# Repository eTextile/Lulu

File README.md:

# Lulu-MCU

**Programming light into textile**

Lulu is a hardware solution that interfaces between an LED light source, an optic fiber strand or bundle and soft circuit connections.
Providing an optic fiber connection toolset and workflow for E-Textiles and Wearable Technology applications.

### About The project
Lulu is providing a simple, reliable toolset for people who want to use side glow optical fibers in their eTextile and wearable projects.
Use of light in textile and fashion design is becoming more and more common and many schools started to teach this subject as a part of their textile design curriculum.
Optic fibers could be embedded in textiles as embroidery, in weaving, knitting and knotting process and many textile designs have been realized in recent years.
But often the designers lack the toolset for connecting the light sources with the embedded optic fibers, resulting in re-purposing bulky connectors and technology and hiding them behind the textiles.
Currently, each designer has to come up with their own re-purposed or DIY solution.
Lulu is a connector that optimizes the efficiency of the connection between the light source and the optical fibers to get a strong illumination.
Instead of struggling to solve the light source and connection problem, the designer can concentrate on the aesthetic and textile making process issues.

### Lulu branches
- **Lulu-star (master)**
  - This branch provide a tiny PCB with a 200mA LED, PWM driver and an optic fiber connector.
- **Lulu-daisy**
  - This branch provide a tiny PCB with an addressable LED (WS2812-mini, Dotstar, etc) and an optic fiber connector.
- **Lulu-MCU**
  - This branch provide a tiny PCB with a built in MCU (ATTiny10) that allow one-wire communication bus system.
- **Lulu**
  - This branch provide a motherboard (Lucette) that drive up to 16 Lulu that only contain a power LED and an optic fiber connector.

### Development tools & DOCs
 * **Web page**: [http://lulu.eTextile.org](http://lulu.eTextile.org "The project Web page")
 * **Kobakant web page**: [http://www.kobakant.at/KOBA/lulu-developments](http://www.kobakant.at/KOBA/lulu-developments "Kobakant project Web page")
 * **Repository**: [https://github.com/eTextile/Lulu/tree/master](https://github.com/eTextile/Lulu/tree/master "The project repository")
 * **License**: [CC-BY-SA](https://github.com/eTextile/Lulu/blob/master/LICENSE "See the Lulu license project")
 * **Video**: [Lulu project by Hannah](https://www.youtube.com/watch?v=drAoLd_eUWk "Lulu project Introduction")
 * **Video**: [Lulu project by Maurin](https://vimeo.com/249171264 "eTextile bus solution")
 * **Mail**: [lulu@etextile.org](mailto:lulu@etextile.org "eMail us")
 * **IRC**: [Riot](https://vector.im/develop/#/room/#lulu:matrix.org "Join us on the chat to collaborate in the development")
 * **Pictures**: [Flickr](https://www.flickr.com/groups/3908991@N25/ "Share your Lulu pictures project")

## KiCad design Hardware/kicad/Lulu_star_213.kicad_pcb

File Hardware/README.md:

# Lulu-MCU / Hardware
**Programming light into textile**

# Lulu-MCU

## Hardware design
This branch of the Lulu project is using a 200mA power LED with current current circuitry.
As the project is focussing on embedded electronics we chosed an high power LED ; OSRAM OSLON SX seeking 200 mA/h 
Then it can be 5 hour of autonomy with a 1000 mA Lypo battery.
The LED is also providing a narrow angle (60°) this helps to focus the light in to the optic fiber wafer.
    See datasheet: https://github.com/eTextile/Lulu/blob/master/Hardware/DOCs/LY_CN5M.pdf
The brass tube connector have been selected to fit the outer diameter of the LED optics.
The PCB triangle shape have been selected to fit the zero waste production process.
All the components are SMD package to reduce the size and price of th PCB.
We have been experiencing a new way to hand solder the LED on the edge of the PCB but it is still not so handy.
Custom tooling will be designed and tested to help in that soldering process.

## Release notes
### Lulu-MCU 4.0.0
- Initial release (forked from Lulu-star 2.1.3)

## Lulu-MCU connecting
- [VCC] (+) 3.3 to 5 Voltes
- [GND] (-) GND
- [DATA] oneWire data bus

        +---+--------------+-------------------+-----
        |   |              |                   |
    + __|__ |              |                   |
    -  ___  |              |                   |
        |   |              |                   |
        +---|--------------|--+----------------|--+--
        |   |              |  |                |  |
        |   |            __|__|__            __|__|__
       _|___|_           \ +  - /            \ +  - /
      | +   - |           \    /              \    /
      |   M   |            \  /                \  /
      |   C   |             \/                  \/
      |   U   |              |                   |
      |       |--------------------- DATA ------------
      |_______|

## Lulu-MCU Powering
The Lulu-MCU board must be powered with a voltage betwin 3.3V to 5V.
DO NOT USE 3V single coin battery - voltage is too low and it will not work for long.
Prefer the use of rechargeable Lipo battery with small Lipo charger.
- https://www.powerstream.com/thin-primary-lithium.htm
- Charger technology
- Low discharge protection

## Lulu-MCU built-in LED driver
### Constant current source circuitry

**References**
- https://learn.adafruit.com/pixie-3-watt-smart-chainable-led-pixels/design
- http://www.instructables.com/id/Power-LED-s---simplest-light-with-constant-current/
- https://scienceprog.com/building-simple-constant-current-power-led-driver/
- http://www.pcbheaven.com/userpages/LED_driving_and_controlling_methods/?topic=worklog&p=3

### Circuit part list
| Designator                                      | MPN                       | Package                | Price per unit | Weblink                |
| ----------------------------------------------- | ------------------------- | -----------------------|--------------- |------------------------|
| Power LED / OSRAM 200mA                         | LY CN5M                   |                        | 0.65 $         | [LY-CN5M](https://fr.aliexpress.com/item/OSRAM-OSLON-SX-High-Power-LED-0-5W-3030-Yellow-LY-CN5M/32865040281.html?spm=a2g0s.9042311.0.0.27426c371XVtDl) |
| Q1 - large N-channel MOSFET                     | IRLML2060TRPBF            | SOT-23                 | 0,126 €        | [IRLML2060TRPBF](https://www.digikey.com/product-detail/en/infineon-technologies/IRLML2060TRPBF/IRLML2060TRPBFCT-ND/2271917) |
| T1 - small NPN transistor                       | MMBT2222A                 | SOT-23                 | 0,0412 €       | [MMBT2222A](https://www.digikey.com/product-detail/en/diodes-incorporated/MMBT2222A-7-F/MMBT2222A-FDICT-ND/815723) |
| R1 - 47k-ohm resistor                           | RT0603DRD0747KL           | 0603                   | 0,0147 €       | [R-47k-ohm ](https://www.digikey.com/product-detail/en/yageo/RT0603DRD0747KL/311-47KDCT-ND/1035828) |
| R2 - current set resistor - 2.7 ohms 1/4 watt   |                           | 1206                   | 0,0246 €       | [R-2.7-ohm](https://fr.farnell.com/walsin/wr12w2r70ftl/resist-couche-epaisse-2-7r-1-0/dp/2668305) |
| R3 - 10k pull-down resistor                     | RT0603DRD0710KL           | 0603                   | 0,     €       | [R-10k-ohm](https://www.digikey.com/product-detail/en/yageo/RT0603DRD0710KL/311-10KDCT-ND/1035680) |
| ATTiny10                                        |                           | SOT-                   | 0,     €       | [ATTiny10](...) |

**R2** is used to set the current limit and this doesn't depends on the voltage supply VDD.
**Q1** is used as a variable resistor. **Q1** starts out turned on by **R1**.
**T1** is used as an over-current sensing switch, and **R2** is the "sense resistor" that triggers **T1** when too much current is flowing.
The main current flow is through the LED's, through **Q1**, and through **R2**.
When too much current flows through **R2**, **T1** will start to turn on, which starts turning off **Q1**. Turning off **Q1** reduces the current through the LED's and **R2**.
So we've created a **feedback loop**, which continuously tracks the current and keeps it exactly at the set point at all times.
The NPN transistors **T1** have a specified 0.6V drop between base and emitter when on.
This means the voltage across their respective shunt resistors **R2** will always be 0.6V.
According to Ohm’s law, this means that the current through them will be '0.6 V / 2.7 Ohm', or about 222mA.

## PCB manufacturing characteristics
  - Base Material : FR-4 TG13
  - No. of Layers : 2 layers
  - PCB Thickness : 1 mm
  - PCB Color : Yelow
  - Surface Finish : HASL
  - Minimum Solder Mask Dam : 0.4 mm
  - Copper Weight : 1oz (35 µm)
    - For 300 mA we nead 0.15mm copper traces (https://www.4pcb.com/trace-width-calculator.html)
  - Minimum Drill Hole Size : 0.3 mm
  - Trace Width / Spacing : 5/5 mil
  - Blind or Buried Vias : NO
  - Plated Half-holes / Castellated Holes : YES
  - Impedance Control : NO

### Extra Part list
| Part                       | REF                      | Price per unit   | Weblink        |
| -------------------------- | ------------------------ | -----------------|--------------- |
| Brass tube                 | 2 mm Hole 5-10 mm Length |                  |                |
| JTE connector              | 1.5 / 8 mm               |                  |                |
| Optical fibres PMMA        | 0.25 mm x 35 pce         |                  |                |
| Optical fibres TPU         | 1.5, 2, 3 mm             |                  |                |
| Optical fibres tube + core |                          |                  | [www.leds-and-more.de](https://www.leds-and-more.de/catalog/15mm-lwl-lichtwellenleiter-lichtleiter-seitlich-leuchtend-p-1937.html?osCsid=2me5dl4q5amcvgb6tnbqfd87i5) |
| eTextile bus               |                          |                  |                |

## TODO
- [ ] Add ATTiny10 ont the KiCad desin
- [ ] Add POGO PINs on the PCB to flash the ATTiny10
- [ ] Change the PCB shape to put the tube angle to 90° from the e-Textile bus
- [ ] cool ref: https://hackaday.io/project/179554-tinyicoc

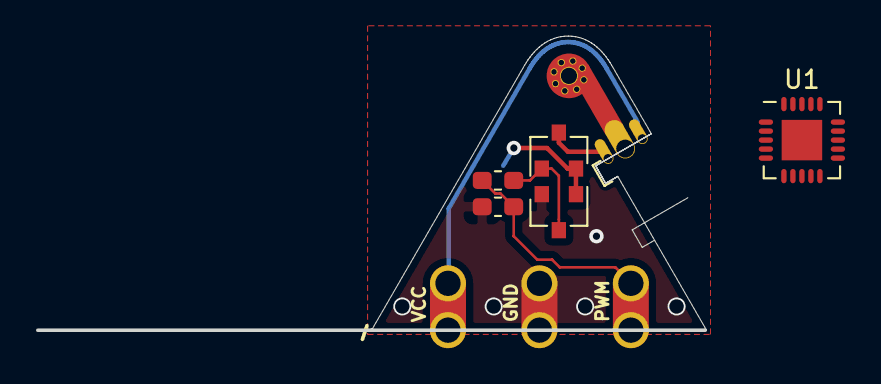
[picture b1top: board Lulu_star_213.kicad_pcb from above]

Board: 2 copper layers, 18.6 x 16.3 mm, 8 parts (1 on the bottom side), 7 nets.

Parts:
J1: Conn_01x03_Female; Lulu_plug_3_spaced
LED1: LED_PAD; Lulu_side_LED
Q1: Q_NMOS_GSD; SOT-23
R1: 47 K; R_0603_1608Metric_Pad1.05x0.95mm_HandSolder
R2: 2.7 Ohm; R_1206_3216Metric_Pad1.42x1.75mm_HandSolder
R3: 10 K; R_0603_1608Metric_Pad1.05x0.95mm_HandSolder
T1: Q_NPN_BEC; SOT-23
U1: ATtiny85-20MU; QFN-20-1EP_4x4mm_P0.5mm_EP2.25x2.25mm

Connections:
+3V3: J1.1, LED1.2
/PWM: J1.3, R1.2, R3.1
GND: J1.2, LED1.3, R2.2, R3.2, T1.2
unnamed: LED1.1, Q1.3
unnamed: Q1.1, R1.1, T1.3
unnamed: Q1.2, R2.1, T1.1
unnamed: U1.8, U1.21

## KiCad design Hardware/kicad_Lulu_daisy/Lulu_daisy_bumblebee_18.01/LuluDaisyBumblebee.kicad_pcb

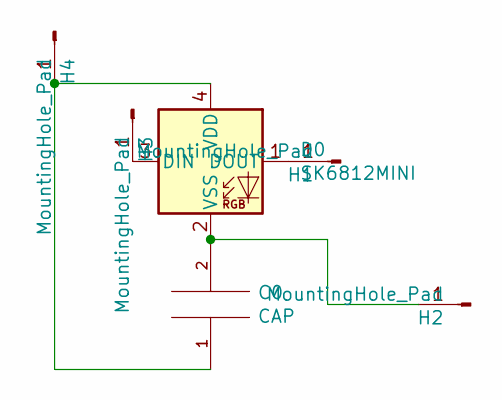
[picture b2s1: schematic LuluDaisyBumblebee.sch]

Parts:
C0: CAP; C_0603_HandSoldering
D0: SK6812MINI; LED_SK6812MINI_PLCC4_3.5x3.5mm_P1.75mm_CUSTOM
H1, H2, H3, H4: MountingHole_Pad; bee_pad

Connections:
unnamed: C0.1, D0.4 (VDD), H4.1
unnamed: C0.2, D0.2 (VSS), H2.1
unnamed: D0.1 (DOUT), H1.1
unnamed: D0.3 (DIN), H3.1

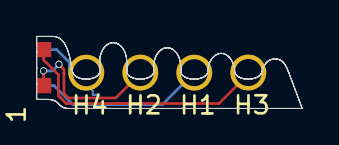
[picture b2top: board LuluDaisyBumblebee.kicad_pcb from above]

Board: 2 copper layers, 14.7 x 4.0 mm, 6 parts (1 on the bottom side), 4 nets.

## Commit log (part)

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2014-05-06 Update lucette_seq.ino
    Optimisation du protocole de communication entre la carte Lucette et un logiciel Pilote réalisé avec PureData. Pour contrôler une sortie de la carte Lucette il faut utiliser trois octets :
    le premier pour définir la LED à actualiser le second et le troisième pour définir la valeur 12 bits (0-4095) qui correspond à l'intensité de la LED.
2014-05-06 Update README.md
    Fonctions de la carte Lucette / fork du projet Arduino
2014-05-07 Update README.md
    cleaning
2014-05-07 Create LEDs_seq
2014-05-07 Create Seq_master
2014-05-07 Rename LEDs_seq to set_seq
2014-05-10 Update Seq_master
    bug fix
2014-05-17 Update Lucette_seq.ino
    Bug fix in ledUpdate();
2014-05-21 Update Lucette_seq.ino
    adding new parcing methode, readBytesUntil();
2014-05-22 Update Lucette_seq.ino
    Bug fix
2014-06-04 Update Lucette_seq.ino
    Bug fix.
    Add new communication
2014-06-06 Update Seq_master
    New new!
2014-06-29 Rename Seq_master to Seq_master.pd
2014-06-29 Rename set_seq to set_seq.pd
2014-06-29 Rename set_seq.pd to led_seq.pd
2014-07-01 Update Lucette_seq.ino
    add ERROR Handling if a LED is diconnected.
2015-10-08 added eagle boards
2016-10-13 clean up
2016-10-20 clean README
2016-10-20 add Lulu PCB
2016-10-20 re-organised README
2016-10-20 clean formating
2016-10-20 clear formatting
2016-11-04 Added tutorial link
2017-01-15 Fixed URL link
2017-12-13 Suppressed pictures
2017-12-13 Added pictures
2017-12-13 minor changes
2017-12-13 Added local pictures
2017-12-13 Initial commit from Lucette branche
2017-12-13 Removed PureData Driver
2018-01-10 Added test code for ATTiny10
2018-01-12 Added TPI programmer info...
2018-01-31 Adeed 1-wire github project ref
2018-02-04 Renamed foldes
2018-02-05 Added project overview & social media links
2018-02-05 Moved text from master readMe to folder readMe
2018-02-05 Less is more
2018-02-05 Markdown syntax cleanUp
2018-02-05 Mismatch with hard and soft
2018-02-05 Added picture
2018-02-05 Added link of original work
2018-02-05 Added protocol explanation
2018-02-05 Removed ATTiny10 test files
2018-02-05 Added initial firmware forked from Kevin Cuzner
2018-02-05 Updated introduction
2018-02-05 Removed pictures and old files
2018-02-05 Added TODO list
2018-02-05 Added ATTiny10 datasheet
2018-02-05 Removed hided file
2018-02-06 Added eMail & videos links
2018-02-06 play with Markdown
2018-02-09 Added all Branch to the README
2018-02-26 Added comments
2018-02-26 Updated webpage URL
2018-02-26 Added web link of 1-wire lib for teensy
2018-02-26 Added array for part list
2018-02-26 Added description
2018-02-26 Updated TODO list
2018-02-26 Updated pull-up resistor value
2018-02-27 Added Markdown liste select
2018-02-27 Added price per unit
2018-03-18 Added new web page link
2018-03-18 Added OpenJSCAD submodule
2018-03-18 Removed OpenJSCAD
2018-03-18 Added OpenJSCAD-web
2018-03-18 Playing with webPage
2018-03-18 Removed TODO
2018-03-19 Added kobakant webpage
2018-04-01 syntax errors
2018-05-02 Removed CNAME
2018-05-02 Added Bootstrap web page
2018-05-07 Removed credit & added new picture
2018-05-07 Added .gitignore
2018-05-08 Minor change
2018-05-09 Updated Branches name
2018-05-09 Updated Upverter web link
2018-05-09 Removed MCU files
2018-05-09 Updated README with new diagram
2018-05-09 Added warning
2018-05-09 Updatad schematics for daisy-chained
2018-05-10 Added Lulu-daisy branche
2018-05-11 Added schematic drawing
2018-05-11 Removed Software file
2018-05-11 Removed .gitmodules
2018-05-12 Removed unused file
2018-05-12 Update branches
2018-05-13 Added 3D openscad
2018-05-14 Updated measurements
2018-05-15 Updated branch list
2018-05-15 Removed unused files
2018-05-15 Removed unused folder
2018-05-15 Updated title
2018-05-18 is back
2018-05-18 footprint_connection.jpg
2018-05-18 Added footprint_connection.jpg
2018-05-20 Added footprint connection picture
2018-05-21 Updated Part list
2018-05-21 Updated Project content
2018-05-28 Small fix
2018-06-03 Added driver circut picture
2018-06-04 Added connector
2018-06-04 Added link to new PCB design
2018-06-11 Added more explanations
2018-06-11 Added datasheet
2018-06-12 Updatad part list
2018-06-12 Removed resistor value R1
2018-06-26 added PCB specs
2018-06-26 Added GERBER files
2018-08-03 Added LED Weblink
2018-08-21 Added new LED datasheet
2018-08-21 Removed unused LED datasheet
2018-08-21 Added KiCad file
2018-08-21 Added file naming conventions
2018-08-21 Renamed folder
2018-08-21 Removed - kicad bad config
2018-08-21 Fixed weblink
2018-08-21 Added circuit part list weblinks
2018-08-30 PCB in progress
2018-08-30 Added e-textile bus datasheet
2018-08-30 Added PCB shape path
2018-08-30 Removed openScad 3D file -> 3D is now done with KiCad
2018-08-31 Renamed file
2018-08-31 TODO: Add this file to the .gitignore
2018-08-31 .gitignore file
2018-09-02 Added brass tube pad footprint
2018-09-02 Updated Lulu 212 path
2018-09-02 Added file
2018-09-03 Added new file for 2D-3D components
2018-09-03 Moved file to Hardware/kicad_Lulu_star/Lulu_star_212/Library/
2018-09-03 Added PCB pin fonctions top & bottom
2018-09-04 Added some info for trace width calculation
2018-09-04 Routing done
2018-09-04 Fixed 3D XYZ pos for KiCad import
2018-09-05 Updated pictures size
2018-09-06 Added Pull down resistor on PWM pin
2018-09-12 Correct the thermal pad GND connection
2018-09-14 Updated ground plane
2018-09-18 Move down all components of the PCB
2018-09-21 Added ziped GERBER files for production
2018-09-21 Updated clearance to 0.2
2018-09-21 Added Software folder for Arduino examples
2018-09-22 Start
2018-09-22 Updated library path with relative position
2018-10-09 test
2018-10-24 Added new Arduino examples
2018-10-25 Added - Branche naming conventions
2018-10-25 Added releases info
2018-10-25 Added README to list the the Arduino examples
2018-10-26 Added bigger path
2018-11-07 Updated syntax
2018-11-19 Added Updated Lulu_star_213
2018-11-19 Removed Lulu_star_212
2018-11-19 In production
2018-11-19 Added BOM
2018-11-19 Updated BOM
2018-11-19 Updated Release notes for V2.1.3
2018-11-23 Updated schematics & picture
2018-11-23 CleanUp syntax
2018-11-23 Updated picture
2019-01-08 adding lulu daisy to the master branch
2019-01-17 Updatad exemples
2019-01-17 Removed .DS_Store
2019-01-17 Removed Lulu-daisy txt
2019-01-17 Added design specs
2019-01-17 Removed TODO list
2019-01-17 Added new design
2019-01-17 Removed unused docs
2019-01-17 Added library Weblink
2019-01-18 Update Lulu-star picture
2019-01-18 Added Lulu-star picture to the carousel
2019-01-31 Updated TODO list
2019-01-31 added .txt extension
2019-01-31 mv Software>Firmware
2019-01-31 Added Arduino compatibility
2019-01-31 Added new docs
2019-01-31 Updatad
2019-01-31 Forked from Lulu-star
2019-01-31 Updated TPI ASCii
2019-02-01 CleanUP
2019-02-01 New picture
2019-02-04 Working prototype
2019-02-04 Set LED to 200mA
2019-02-04 Added Lulu_ID & Lulu_value to the oneWire bus comm
2019-02-05 Added BRODCAST ID
2019-02-07 Added top level communication protocol. attempt to configure the hardware on the fly to handle 16 bit Hardware PWM & 1-Wire Hardware decoder
2019-02-07 Added DOCs
2019-02-08 Merged 1-Wire & embedded LED fading pattern generator
2019-02-11 added non blocking delay & correct some bugs. Working as a charme
2019-02-11 Improved LEDs control sync
2019-02-25 swatch demo code
2019-02-26 Routing in process
2019-02-26 Moved fies
2019-02-26 Updated for security
2019-03-19 Updated Kobakant/lulu project URL
2019-03-19 Moved Lulu_daisySwatch.ino to the Lulu-daisy branch
2019-03-19 Added Lulu_daisySwatch.ino
2019-04-12 testing
2019-04-15 Updated hardware design explanation
2019-04-15 Under testing
2019-04-15 Under routing
2019-04-15 Routing
2019-04-15 Added doc
2019-04-15 Updatad .pdf
2019-04-15 back in time
2019-04-15 Added .odp (libre office) source file
2019-04-18 Added Picture of the 1-wire bus with ATTiny-10
2019-11-14 Updatad picture
2019-11-14 Updated title typo
2019-11-14 Bump mixin-deep from 1.3.1 to 1.3.2 in /docs
    Bumps [mixin-deep](https://github.com/jonschlinkert/mixin-deep) from 1.3.1 to 1.3.2.
    - [Release notes](https://github.com/jonschlinkert/mixin-deep/releases)
    - [Commits](https://github.com/jonschlinkert/mixin-deep/compare/1.3.1...1.3.2)
2019-11-14 Bump lodash.mergewith from 4.6.1 to 4.6.2 in /docs
    Bumps [lodash.mergewith](https://github.com/lodash/lodash) from 4.6.1 to 4.6.2.
    - [Release notes](https://github.com/lodash/lodash/releases)
    - [Commits](https://github.com/lodash/lodash/commits)
2019-11-14 Bump fstream from 1.0.11 to 1.0.12 in /docs
    Bumps [fstream](https://github.com/npm/fstream) from 1.0.11 to 1.0.12.
    - [Release notes](https://github.com/npm/fstream/releases)
    - [Commits](https://github.com/npm/fstream/compare/v1.0.11...v1.0.12)
2019-11-14 Bump handlebars from 4.0.12 to 4.5.2 in /docs
    Bumps [handlebars](https://github.com/wycats/handlebars.js) from 4.0.12 to 4.5.2.
    - [Release notes](https://github.com/wycats/handlebars.js/releases)
    - [Changelog](https://github.com/wycats/handlebars.js/blob/master/release-notes.md)
    - [Commits](https://github.com/wycats/handlebars.js/compare/v4.0.12...v4.5.2)
2019-11-14 Added favicon
2019-11-17 Update typos
2019-11-18 Bump jquery from 3.3.1 to 3.4.0 in /docs
    Bumps [jquery](https://github.com/jquery/jquery) from 3.3.1 to 3.4.0.
    - [Release notes](https://github.com/jquery/jquery/releases)
    - [Commits](https://github.com/jquery/jquery/compare/3.3.1...3.4.0)
2019-11-18 Bump js-yaml from 3.12.1 to 3.13.1 in /docs
    Bumps [js-yaml](https://github.com/nodeca/js-yaml) from 3.12.1 to 3.13.1.
    - [Release notes](https://github.com/nodeca/js-yaml/releases)
    - [Changelog](https://github.com/nodeca/js-yaml/blob/master/CHANGELOG.md)
    - [Commits](https://github.com/nodeca/js-yaml/compare/3.12.1...3.13.1)
2019-11-18 Bump eslint-utils from 1.3.1 to 1.4.3 in /docs
    Bumps [eslint-utils](https://github.com/mysticatea/eslint-utils) from 1.3.1 to 1.4.3.
    - [Release notes](https://github.com/mysticatea/eslint-utils/releases)
    - [Commits](https://github.com/mysticatea/eslint-utils/compare/v1.3.1...v1.4.3)
2019-11-18 Testing button
2019-11-18 Updated button
2019-12-08 Renamed github link
2019-12-12 Berlin
2020-03-14 Bump acorn from 6.0.7 to 6.4.1 in /docs
    Bumps [acorn](https://github.com/acornjs/acorn) from 6.0.7 to 6.4.1.
    - [Release notes](https://github.com/acornjs/acorn/releases)
    - [Commits](https://github.com/acornjs/acorn/compare/6.0.7...6.4.1)
2020-04-16 Bump https-proxy-agent from 2.2.1 to 2.2.4 in /docs
    Bumps [https-proxy-agent](https://github.com/TooTallNate/node-https-proxy-agent) from 2.2.1 to 2.2.4.
    - [Release notes](https://github.com/TooTallNate/node-https-proxy-agent/releases)
    - [Commits](https://github.com/TooTallNate/node-https-proxy-agent/compare/2.2.1...2.2.4)
2020-04-29 Bump jquery from 3.4.0 to 3.5.0 in /docs
    Bumps [jquery](https://github.com/jquery/jquery) from 3.4.0 to 3.5.0.
    - [Release notes](https://github.com/jquery/jquery/releases)
    - [Commits](https://github.com/jquery/jquery/compare/3.4.0...3.5.0)
2020-09-04 Bump node-sass from 4.11.0 to 4.13.1 in /docs
    Bumps [node-sass](https://github.com/sass/node-sass) from 4.11.0 to 4.13.1.
    - [Release notes](https://github.com/sass/node-sass/releases)
    - [Changelog](https://github.com/sass/node-sass/blob/master/CHANGELOG.md)
    - [Commits](https://github.com/sass/node-sass/compare/v4.11.0...v4.13.1)
2020-09-06 Bump handlebars from 4.5.2 to 4.7.6 in /docs
    Bumps [handlebars](https://github.com/wycats/handlebars.js) from 4.5.2 to 4.7.6.
    - [Release notes](https://github.com/wycats/handlebars.js/releases)
    - [Changelog](https://github.com/handlebars-lang/handlebars.js/blob/master/release-notes.md)
    - [Commits](https://github.com/wycats/handlebars.js/compare/v4.5.2...v4.7.6)
2020-10-09 Added https
2020-10-09 dirty commit
2021-01-29 Updated form link that was off
